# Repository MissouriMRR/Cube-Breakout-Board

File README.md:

# Cube-Breakout-Board
Breakout board for 80-Pin DF-17 connector on bottom of Cube

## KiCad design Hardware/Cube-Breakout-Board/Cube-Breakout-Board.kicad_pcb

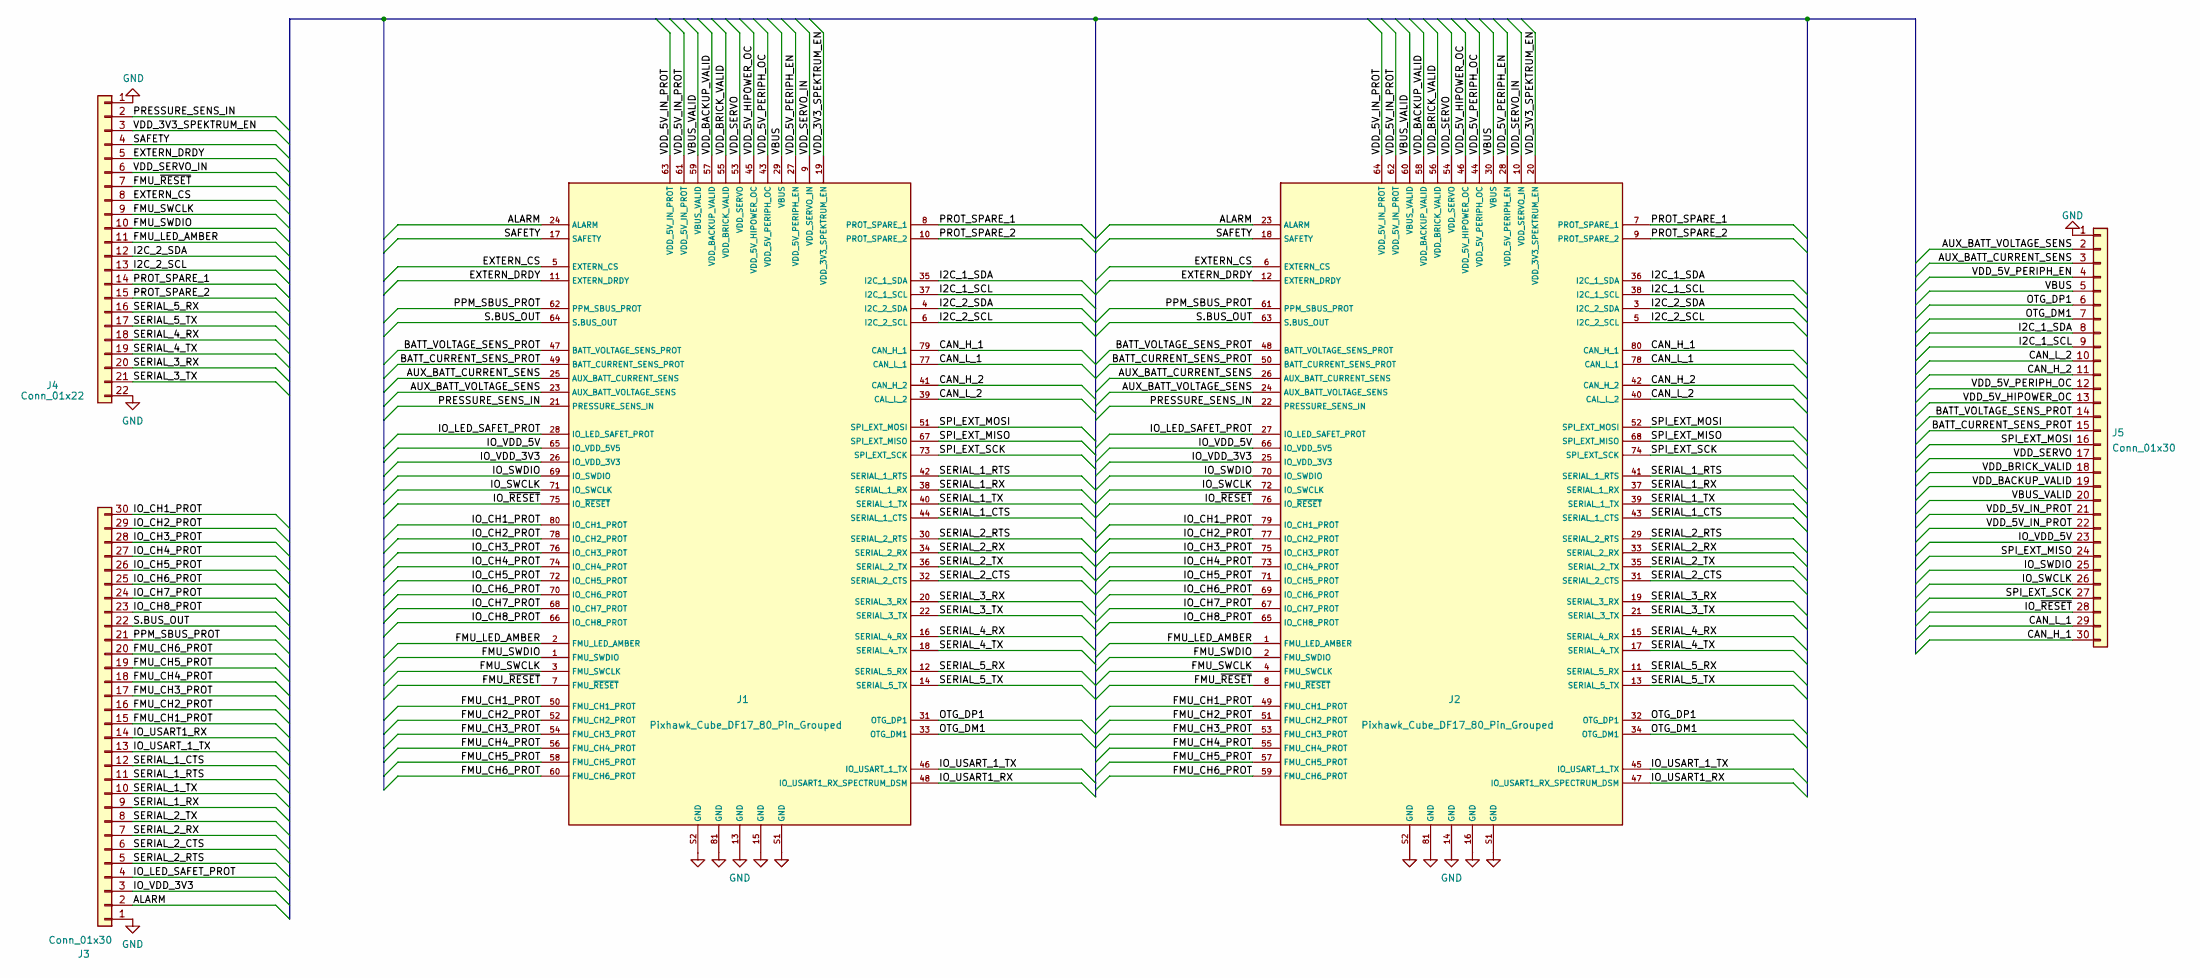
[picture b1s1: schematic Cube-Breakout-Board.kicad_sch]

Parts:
J1, J2: Pixhawk_Cube_DF17_80_Pin_Grouped; Cube_DF17_Mount
J3, J5: Conn_01x30; PinSocket_1x30_P2.54mm_Vertical
J4: Conn_01x22; PinSocket_1x22_P2.54mm_Vertical

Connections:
/ALARM: J1.24 (ALARM), J2.23 (ALARM), J3.2
/AUX_BATT_CURRENT_SENS: J1.25 (AUX_BATT_CURRENT_SENS), J2.26 (AUX_BATT_CURRENT_SENS), J5.3
/AUX_BATT_VOLTAGE_SENS: J1.23 (AUX_BATT_VOLTAGE_SENS), J2.24 (AUX_BATT_VOLTAGE_SENS), J5.2
/BATT_CURRENT_SENS_PROT: J1.49 (BATT_CURRENT_SENS_PROT), J2.50 (BATT_CURRENT_SENS_PROT), J5.15
/BATT_VOLTAGE_SENS_PROT: J1.47 (BATT_VOLTAGE_SENS_PROT), J2.48 (BATT_VOLTAGE_SENS_PROT), J5.14
/CAN_H_1: J1.79 (CAN_H_1), J2.80 (CAN_H_1), J5.30
/CAN_H_2: J1.41 (CAN_H_2), J2.42 (CAN_H_2), J5.11
/CAN_L_1: J1.77 (CAN_L_1), J2.78 (CAN_L_1), J5.29
/CAN_L_2: J1.39 (CAL_L_2), J2.40 (CAL_L_2), J5.10
/EXTERN_CS: J1.5 (EXTERN_CS), J2.6 (EXTERN_CS), J4.8
/EXTERN_DRDY: J1.11 (EXTERN_DRDY), J2.12 (EXTERN_DRDY), J4.5
/FMU_CH1_PROT: J1.50 (FMU_CH1_PROT), J2.49 (FMU_CH1_PROT), J3.15
/FMU_CH2_PROT: J1.52 (FMU_CH2_PROT), J2.51 (FMU_CH2_PROT), J3.16
/FMU_CH3_PROT: J1.54 (FMU_CH3_PROT), J2.53 (FMU_CH3_PROT), J3.17
/FMU_CH4_PROT: J1.56 (FMU_CH4_PROT), J2.55 (FMU_CH4_PROT), J3.18
/FMU_CH5_PROT: J1.58 (FMU_CH5_PROT), J2.57 (FMU_CH5_PROT), J3.19
/FMU_CH6_PROT: J1.60 (FMU_CH6_PROT), J2.59 (FMU_CH6_PROT), J3.20
/FMU_LED_AMBER: J1.2 (FMU_LED_AMBER), J2.1 (FMU_LED_AMBER), J4.11
/FMU_SWCLK: J1.3 (FMU_SWCLK), J2.4 (FMU_SWCLK), J4.9
/FMU_SWDIO: J1.1 (FMU_SWDIO), J2.2 (FMU_SWDIO), J4.10
/FMU_~RESET: J1.7 (FMU_~RESET), J2.8 (FMU_~RESET), J4.7
/I2C_1_SCL: J1.37 (I2C_1_SCL), J2.38 (I2C_1_SCL), J5.9
/I2C_1_SDA: J1.35 (I2C_1_SDA), J2.36 (I2C_1_SDA), J5.8
/I2C_2_SCL: J1.6 (I2C_2_SCL), J2.5 (I2C_2_SCL), J4.13
/I2C_2_SDA: J1.4 (I2C_2_SDA), J2.3 (I2C_2_SDA), J4.12
/IO_CH1_PROT: J1.80 (IO_CH1_PROT), J2.79 (IO_CH1_PROT), J3.30
/IO_CH2_PROT: J1.78 (IO_CH2_PROT), J2.77 (IO_CH2_PROT), J3.29
/IO_CH3_PROT: J1.76 (IO_CH3_PROT), J2.75 (IO_CH3_PROT), J3.28
/IO_CH4_PROT: J1.74 (IO_CH4_PROT), J2.73 (IO_CH4_PROT), J3.27
/IO_CH5_PROT: J1.72 (IO_CH5_PROT), J2.71 (IO_CH5_PROT), J3.26
/IO_CH6_PROT: J1.70 (IO_CH6_PROT), J2.69 (IO_CH6_PROT), J3.25
/IO_CH7_PROT: J1.68 (IO_CH7_PROT), J2.67 (IO_CH7_PROT), J3.24
/IO_CH8_PROT: J1.66 (IO_CH8_PROT), J2.65 (IO_CH8_PROT), J3.23
/IO_LED_SAFET_PROT: J1.28 (IO_LED_SAFET_PROT), J2.27 (IO_LED_SAFET_PROT), J3.4
/IO_SWCLK: J1.71 (IO_SWCLK), J2.72 (IO_SWCLK), J5.26
/IO_SWDIO: J1.69 (IO_SWDIO), J2.70 (IO_SWDIO), J5.25
/IO_USART1_RX: J1.48 (IO_USART1_RX_SPECTRUM_DSM), J2.47 (IO_USART1_RX_SPECTRUM_DSM), J3.14
/IO_USART_1_TX: J1.46 (IO_USART_1_TX), J2.45 (IO_USART_1_TX), J3.13
/IO_VDD_3V3: J1.26 (IO_VDD_3V3), J2.25 (IO_VDD_3V3), J3.3
/IO_VDD_5V: J1.65 (IO_VDD_5V5), J2.66 (IO_VDD_5V5), J5.23
/IO_~RESET: J1.75 (IO_~RESET), J2.76 (IO_~RESET), J5.28
/OTG_DM1: J1.33 (OTG_DM1), J2.34 (OTG_DM1), J5.7
/OTG_DP1: J1.31 (OTG_DP1), J2.32 (OTG_DP1), J5.6
/PPM_SBUS_PROT: J1.62 (PPM_SBUS_PROT), J2.61 (PPM_SBUS_PROT), J3.21
/PRESSURE_SENS_IN: J1.21 (PRESSURE_SENS_IN), J2.22 (PRESSURE_SENS_IN), J4.2
/PROT_SPARE_1: J1.8 (PROT_SPARE_1), J2.7 (PROT_SPARE_1), J4.14
/PROT_SPARE_2: J1.10 (PROT_SPARE_2), J2.9 (PROT_SPARE_2), J4.15
/S.BUS_OUT: J1.64 (S.BUS_OUT), J2.63 (S.BUS_OUT), J3.22
/SAFETY: J1.17 (SAFETY), J2.18 (SAFETY), J4.4
/SERIAL_1_CTS: J1.44 (SERIAL_1_CTS), J2.43 (SERIAL_1_CTS), J3.12
/SERIAL_1_RTS: J1.42 (SERIAL_1_RTS), J2.41 (SERIAL_1_RTS), J3.11
/SERIAL_1_RX: J1.38 (SERIAL_1_RX), J2.37 (SERIAL_1_RX), J3.9
/SERIAL_1_TX: J1.40 (SERIAL_1_TX), J2.39 (SERIAL_1_TX), J3.10
/SERIAL_2_CTS: J1.32 (SERIAL_2_CTS), J2.31 (SERIAL_2_CTS), J3.6
/SERIAL_2_RTS: J1.30 (SERIAL_2_RTS), J2.29 (SERIAL_2_RTS), J3.5
/SERIAL_2_RX: J1.34 (SERIAL_2_RX), J2.33 (SERIAL_2_RX), J3.7
/SERIAL_2_TX: J1.36 (SERIAL_2_TX), J2.35 (SERIAL_2_TX), J3.8
/SERIAL_3_RX: J1.20 (SERIAL_3_RX), J2.19 (SERIAL_3_RX), J4.20
/SERIAL_3_TX: J1.22 (SERIAL_3_TX), J2.21 (SERIAL_3_TX), J4.21
/SERIAL_4_RX: J1.16 (SERIAL_4_RX), J2.15 (SERIAL_4_RX), J4.18
/SERIAL_4_TX: J1.18 (SERIAL_4_TX), J2.17 (SERIAL_4_TX), J4.19
/SERIAL_5_RX: J1.12 (SERIAL_5_RX), J2.11 (SERIAL_5_RX), J4.16
/SERIAL_5_TX: J1.14 (SERIAL_5_TX), J2.13 (SERIAL_5_TX), J4.17
/SPI_EXT_MISO: J1.67 (SPI_EXT_MISO), J2.68 (SPI_EXT_MISO), J5.24
/SPI_EXT_MOSI: J1.51 (SPI_EXT_MOSI), J2.52 (SPI_EXT_MOSI), J5.16
/SPI_EXT_SCK: J1.73 (SPI_EXT_SCK), J2.74 (SPI_EXT_SCK), J5.27
/VBUS: J1.29 (VBUS), J2.30 (VBUS), J5.5
/VBUS_VALID: J1.59 (VBUS_VALID), J2.60 (VBUS_VALID), J5.20
/VDD_3V3_SPEKTRUM_EN: J1.19 (VDD_3V3_SPEKTRUM_EN), J2.20 (VDD_3V3_SPEKTRUM_EN), J4.3
/VDD_5V_HIPOWER_OC: J1.45 (VDD_5V_HIPOWER_OC), J2.46 (VDD_5V_HIPOWER_OC), J5.13
/VDD_5V_IN_PROT: J1.61 (VDD_5V_IN_PROT), J1.63 (VDD_5V_IN_PROT), J2.62 (VDD_5V_IN_PROT), J2.64 (VDD_5V_IN_PROT), J5.21, J5.22
/VDD_5V_PERIPH_EN: J1.27 (VDD_5V_PERIPH_EN), J2.28 (VDD_5V_PERIPH_EN), J5.4
/VDD_5V_PERIPH_OC: J1.43 (VDD_5V_PERIPH_OC), J2.44 (VDD_5V_PERIPH_OC), J5.12
/VDD_BACKUP_VALID: J1.57 (VDD_BACKUP_VALID), J2.58 (VDD_BACKUP_VALID), J5.19
/VDD_BRICK_VALID: J1.55 (VDD_BRICK_VALID), J2.56 (VDD_BRICK_VALID), J5.18
/VDD_SERVO: J1.53 (VDD_SERVO), J2.54 (VDD_SERVO), J5.17
/VDD_SERVO_IN: J1.9 (VDD_SERVO_IN), J2.10 (VDD_SERVO_IN), J4.6
GND: J1.13 (GND), J1.15 (GND), J1.81 (GND), J1.S1 (GND), J1.S2 (GND), J2.14 (GND), J2.16 (GND), J2.81 (GND), J2.S1 (GND), J2.S2 (GND), J3.1, J4.1, J4.22, J5.1

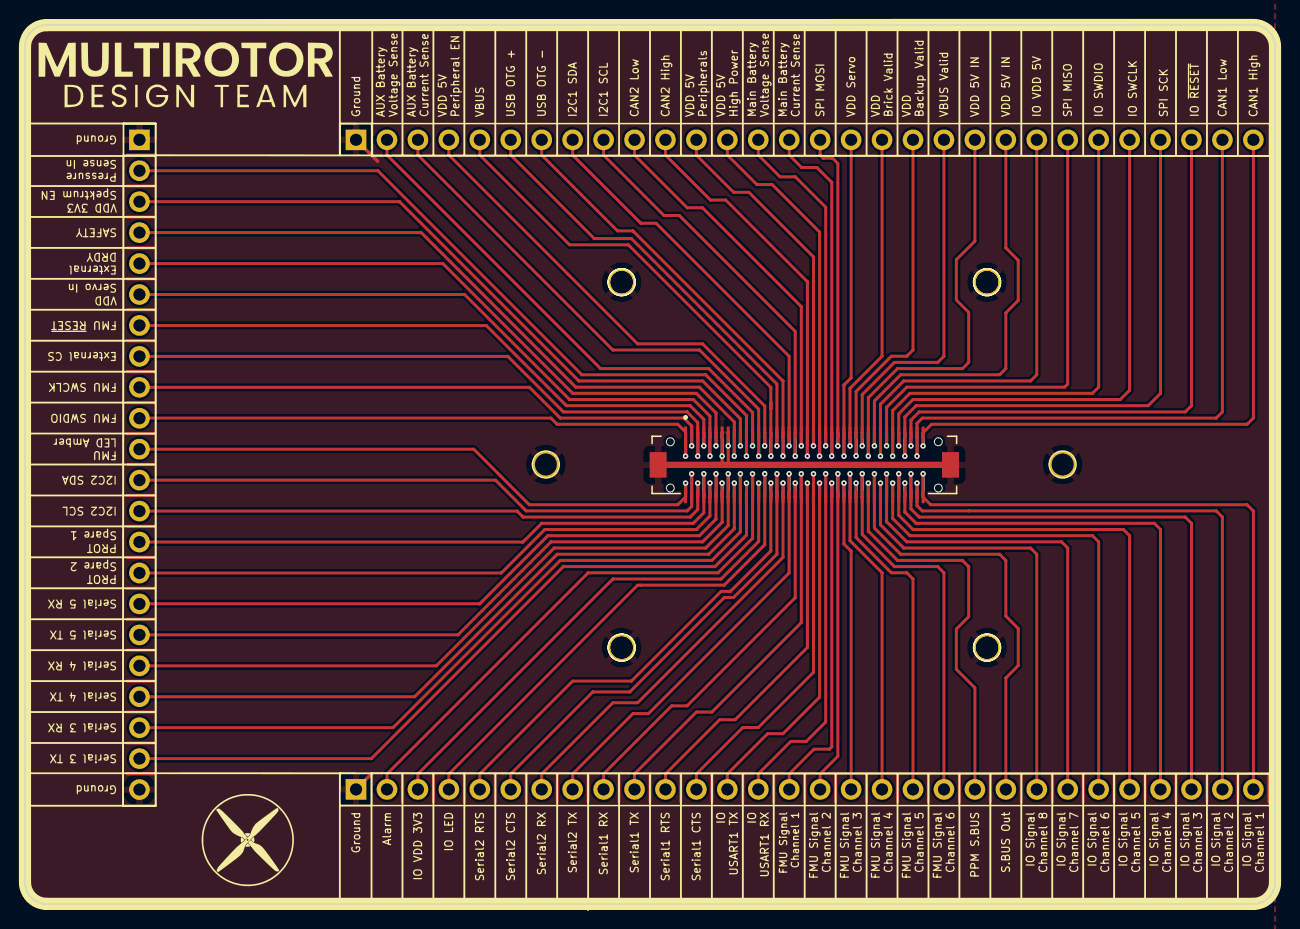
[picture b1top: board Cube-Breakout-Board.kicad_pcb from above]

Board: 2 copper layers, 102.6 x 72.1 mm, 5 parts (1 on the bottom side), 78 nets.

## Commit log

2022-11-14 Created schematic page
2022-11-14 Finished routing, board sizing, silkscreen text
2022-11-15 Expanded layout to fit breadboards
    Need to trim off 3mm of the height to meet max size for JLCPCB
2022-11-26 Added dimensions to PCB
